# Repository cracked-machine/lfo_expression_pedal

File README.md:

## Docker

This project uses the [stm32_dev_docker](https://github.com/cracked-machine/stm32_dev_docker) project to host the developnment environment. Please read the documentation for that project for more information.

## Power consumption

- Power supply voltage: 9V
- LDO Regulator ([AMS1117-3.3](https://datasheet.lcsc.com/lcsc/2204131745_Shenzhen-Fuman-Elec-AMS1117-3-3V_C173386.pdf)): 3.3V
- Power Dissipation (quiescent): 0.034W

## Outputs

|S (sleeve)|T (tip)|R (ring)|
|-|-|-|
|Ground|Signal|3.3V|

## Changelog

### PCB

- REVB
    - Add 3.3v to U1 VREF+ (Pin5).
    -

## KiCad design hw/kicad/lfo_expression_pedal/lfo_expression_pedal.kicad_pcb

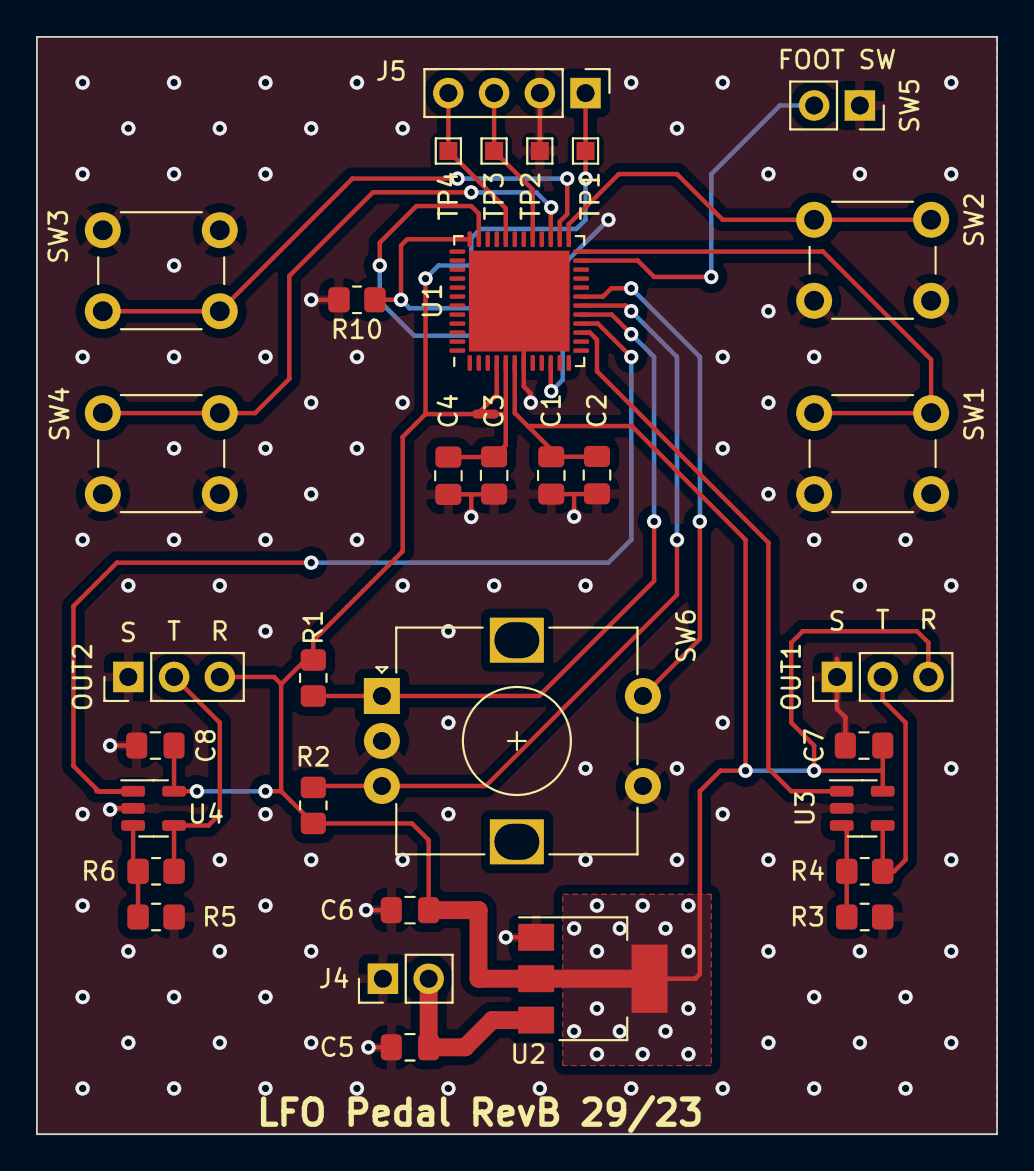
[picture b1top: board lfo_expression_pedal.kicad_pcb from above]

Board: 2 copper layers, 53.3 x 61.0 mm, 35 parts (1 on the bottom side), 23 nets.

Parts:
C1, C3, C7, C8: 100nF; C_0805_2012Metric_Pad1.18x1.45mm_HandSolder
C2: 4.7uF; C_0805_2012Metric_Pad1.18x1.45mm_HandSolder
C4: 1uF; C_0805_2012Metric_Pad1.18x1.45mm_HandSolder
C5, C6: 10uF; C_0805_2012Metric_Pad1.18x1.45mm_HandSolder
J1: Conn_02x05_Odd_Even; PinHeader_2x05_P1.27mm_Vertical_SMD
J2, J6: Conn_01x03; PinHeader_1x03_P2.54mm_Vertical
J4: Conn_01x02; PinHeader_1x02_P2.54mm_Vertical
J5: Conn_01x04; PinHeader_1x04_P2.54mm_Vertical
NT1: NetTie_2; NetTie-2_SMD_Pad0.5mm
R1, R2: 4.7k; R_0805_2012Metric_Pad1.20x1.40mm_HandSolder
R3, R5: DNF; R_0805_2012Metric_Pad1.20x1.40mm_HandSolder
R4, R6: 0R; R_0805_2012Metric_Pad1.20x1.40mm_HandSolder
R10: 10k; R_0805_2012Metric_Pad1.20x1.40mm_HandSolder
SW1, SW2, SW3, SW4: SW_SPST; SW_PUSH_6mm
SW5: SW_SPST; PinSocket_1x02_P2.54mm_Vertical
SW6: RotaryEncoder_Switch; RotaryEncoder_Alps_EC12E-Switch_Vertical_H20mm
TP1, TP2, TP3, TP4: TestPoint; TestPoint_Pad_1.0x1.0mm
U1: STM32G071CBU3; QFN-48-1EP_7x7mm_P0.5mm_EP5.6x5.6mm
U2: LM1117MP-3.3; SOT-223-3_TabPin2
U3, U4: AS321KTR-G1; SOT-23-5

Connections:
+3.3V: C1.1, C2.1, C6.1, C7.1, C8.1, J1.1, J2.3, J5.1, J6.3, NT1.2, R1.1, R2.1, TP1.1, U1.4 (VBAT), U1.6 (VDD), U2.2 (VO), U3.5 (V+), U4.5 (V+)
/dac1_out1: U1.15 (PA4), U3.1 (+)
/dac1_out1_buffered: J6.2, R4.2, U3.4
/dac1_out2: U1.16 (PA5), U4.1 (+)
/dac1_out2_buffered: J2.2, R6.2, U4.4
/foot_sw: SW5.2 (B), U1.23 (PB11)
/i2c1_scl: J5.3, TP3.1, U1.29 (PA9/UCPD1_DBCC1)
/i2c1_sda: J5.4, TP4.1, U1.32 (PA10/UCPD1_DBCC2)
/reset: J1.10, U1.10 (PF2)
/rot_enc_sw: SW6.S1, U1.19 (PB0)
/sys_swclk: J1.4, R10.1, U1.36 (PA14)
/sys_swdio: J1.2, U1.35 (PA13)
/tim3_ch1: R1.2, SW6.A, U1.17 (PA6)
/tim3_ch2: R2.2, SW6.B, U1.18 (PA7)
/user_sw1: SW1.2 (B), U1.24 (PB12)
/user_sw2: SW2.2 (B), U1.25 (PB13)
/user_sw3: SW3.2 (B), U1.26 (PB14)
/user_sw4: SW4.2 (B), U1.27 (PB15)
/vref: C3.1, C4.1, NT1.1, U1.5 (VREF+)
GND: C1.2, C2.2, C3.2, C4.2, C5.2, C6.2, C7.2, C8.2, J1.3, J1.5, J1.9, J2.1, J4.1, J5.2, J6.1, R3.2, R5.2, R10.2, SW1.1 (A), SW2.1 (A), SW3.1 (A), SW4.1 (A), SW5.1 (A), SW6.C, SW6.S2, TP2.1, U1.7 (VSS), U1.49 (VSS), U2.1 (GND), U3.2 (V-), U4.2 (V-)
unnamed: C5.1, J4.2, U2.3 (VI)
unnamed: R3.1, R4.1, U3.3 (-)
unnamed: R5.1, R6.1, U4.3 (-)

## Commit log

2023-07-08 add submodule for stm32 docker images
2023-07-08 add kicad hw project
2023-07-08 add hw production files
2023-07-08 add hw docs
2023-07-08 add python waveform generation scripts
2023-07-08 readme updated with power consumption and out pins notes
2023-07-08 added CMSIS headers
2023-07-08 added system source files
2023-07-08 added linker script
2023-07-08 added main.cpp
2023-07-08 added build cmake config files
2023-07-08 updated readem
2023-07-08 added python pkg requirements
2023-07-08 added path to gnu toolchain to settings
2023-07-08 added swd file
2023-07-08 added config to debug with JLink via USB from within container.
2023-07-09 added low level interrupt functions
2023-07-09 added sysmem(_sbrk) and interrupts source files
2023-07-09 added variables for options. Fixed hard fault by adding ${MCU_CORE} ${THUMB} to linker options
2023-07-18 added submodule
2023-07-18 updated submodule
2023-07-18 DAC triangle output using TIM15 TRGO
2023-07-22 Add 3.3v to U1 VREF+ (Pin5)
